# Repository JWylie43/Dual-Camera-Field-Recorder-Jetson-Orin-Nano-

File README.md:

# Orin Nano Stereo Recorder & Stitcher

An end-to-end field rig for a side-by-side stereo camera on a **Jetson Orin Nano**:
**record** a wide dual-camera feed, **calibrate** the two cameras, and **stitch** the
result into a single cylindrical panorama.

Built around the Arducam B0577 dual global-shutter kit (3840×1200 combined) in a
3D-printed housing, tuned to run for hours outdoors at **30 fps with the CPU
near-idle** (maximum thermal headroom).

---

## Project layout

```
orin-nano-recorder/
├── recorder/            Runs ON THE ORIN — capture + web control panel
│   ├── record.py          hardware-MJPEG → MKV recorder (GStreamer)
│   └── server.py          Flask web panel (Start/Stop, live preview, thermals, snapshots)
├── calibration/         Runs ON YOUR MAC/DESKTOP — ChArUco stereo calibration
│   ├── show_board.py      generate/display the ChArUco board
│   ├── calibrate.py       intrinsics (L+R) + stereo extrinsics from snapshots
│   ├── images/            calibration snapshots (git-ignored)
│   └── *_intrinsics.json, stereo_extrinsics.json   calibration results
├── stitching/           Runs ON YOUR MAC/DESKTOP — panorama stitcher (C++)
│   ├── stitch_pipeline.cpp   calibration-driven cylindrical stitch (image or video)
│   ├── CMakeLists.txt
│   └── include/json.hpp
├── 3d-housing-model/    Printable enclosure (Housing.zip)
└── setup.sh             Orin dependency install / L4T element check
```

## The workflow

1. **Record** on the Orin (`recorder/`) → combined `3840×1200` MKV on the NVMe, and
   full-res calibration snapshots via the web panel's Snapshot button.
2. **Calibrate** on your computer (`calibration/`) → per-camera intrinsics +
   the stereo extrinsic rotation between the two cameras (JSON files).
3. **Stitch** on your computer (`stitching/`) → feed a frame or video + the
   calibration and get a cylindrical panorama. Alignment is driven purely by the
   calibration — no feature matching.

---

# 1. Recorder (on the Orin)

`recorder/record.py` (CLI) and `recorder/server.py` (web panel).

## The one thing to understand first

**The Jetson Orin Nano (and Orin NX) have no hardware video encoder (no NVENC).**
That single fact drives every design decision here:

1. **No `nvv4l2h264enc` / `nvv4l2h265enc`** — they don't exist on this board. H.264/
   H.265 must be done in *software* (x264, CPU-heavy) or you use the **hardware JPEG
   engine (NVJPG)** for MJPEG. This project uses **MJPEG** so the CPU stays idle and
   the board runs cool — the right trade for a hot enclosure. (Files are bigger:
   ~40 GB/hr vs ~7 for H.264. A 500 GB drive holds ~12 hours.)

2. **Capture with `nvv4l2camerasrc`, never `v4l2src`.** Plain `v4l2src` copies every
   9 MB frame on one CPU thread, pegging a core and capping the pipeline at ~28 fps.
   `nvv4l2camerasrc` captures zero-copy into NVMM (GPU memory) → clean, sustained
   30 fps with the CPU barely moving. **This was the single fix that unblocked everything.**

3. **Every queue is `leaky=downstream`.** `nvvidconv` (the VIC) owns a tiny output
   buffer pool; a non-leaky queue behind it grabs all the buffers and *deadlocks* the
   pipeline. Leaky queues drop a frame under pressure instead of stalling.

4. **Stop with SIGINT, never SIGTERM/SIGKILL.** The MKV gets its duration + seek
   index only on a clean end-of-stream (`gst-launch -e` on SIGINT). Kill it any other
   way and you get an unfinalized file (`Duration: N/A`, won't scrub).

## Usage

```bash
cd recorder
# CLI recorder
python3 record.py                 # record until Enter / Ctrl+C
python3 record.py --seconds 30    # fixed duration
python3 record.py --measure --seconds 20         # benchmark fps, no disk write
python3 record.py --seconds 600 --log-thermals   # soak test + tegrastats log
python3 record.py --dry-run       # print the pipeline, don't run

# Web control panel
sudo python3 server.py            # sudo enables the "log thermals to file" toggle
```

Browse from a phone/laptop on the same network to **`http://<orin-ip>:8080`** (find
the IP with `hostname -I`, or use `http://<hostname>.local:8080`). The panel gives you
live preview (idle *and* recording), Start/Stop, elapsed time, live thermals, and a
**Snapshot** button that writes full-res stills to `/mnt/video/calib` for calibration.

## How it works

```
record.py builds & runs a GStreamer pipeline:
  nvv4l2camerasrc → NVMM,UYVY → nvvidconv → I420 → queue(leaky)
    → nvjpegenc → jpegparse → matroskamux → filesink            (the MKV)
  with --preview-port it tees a second branch to a tcpserversink (MJPEG preview)

server.py owns an idle-preview pipeline when stopped, hands the camera to record.py
  on Start, and relays the MJPEG to the browser at /preview.mjpg. Stop = SIGINT =
  clean finalize. The camera is single-open, so one pipeline holds it at a time.
```

## Auto-start on boot (systemd)

Run the panel as a service so it survives reboots. Point it at `recorder/server.py`
and use **`KillSignal=SIGINT`** so `systemctl stop` finalizes the current recording:

```ini
# /etc/systemd/system/camera-rig.service
[Unit]
After=network-online.target
Wants=network-online.target
[Service]
WorkingDirectory=/home/<user>/orin-nano-recorder/recorder
ExecStart=/usr/bin/python3 /home/<user>/orin-nano-recorder/recorder/server.py
Restart=on-failure
User=root
[Install]
WantedBy=multi-user.target
```
```bash
sudo systemctl daemon-reload && sudo systemctl enable --now camera-rig
```

For a **portable** rig, the Orin can broadcast its own Wi-Fi hotspot (NetworkManager
`ipv4.method shared`), so a phone/laptop connects directly at a fixed address with no
router. Give the Orin higher auto-connect priority on your home Wi-Fi so it rejoins
that when in range and falls back to the hotspot in the field.

---

# 2. Calibration (on your computer)

ChArUco-based stereo calibration. **Run on your Mac/desktop, not the Orin** — it needs
`opencv-contrib-python` (the `aruco` module):

```bash
pip install -U opencv-contrib-python numpy
```

## Steps

1. **Board.** `python3 calibration/show_board.py` generates/opens `charuco_board.png`
   (7×10, `DICT_5X5_1000`). **Print it** (matte, glued flat) — printing beats a screen
   (screens add glare/moiré that break detection). **Measure one black square with
   calipers** — you'll pass that size.
2. **Capture.** From the web panel, tap **Snapshot** ~30–40× with the board at varied
   angles/distances. Cover each camera's whole frame **and** get a good batch with the
   board centred where **both** cameras see it (that overlap set drives the extrinsics).
3. **Pull the shots** to `calibration/images/`:
   ```bash
   scp -r <user>@<orin-host>:/mnt/video/calib ./calibration/images
   ```
4. **Calibrate** (from `calibration/`, pass your measured board sizes in mm):
   ```bash
   python3 calibrate.py --square-mm 66.5 --marker-mm 48.5
   ```

Outputs `left_intrinsics.json`, `right_intrinsics.json`, `stereo_extrinsics.json`
(baseline in mm + rotation), plus undistort/rectified sample images.

- Intrinsics are **mount-independent**; extrinsics describe the **fixed housing** —
  re-run if the cameras are disturbed.
- To re-solve only the extrinsics from a fresh overlap batch without recomputing
  intrinsics: `python3 calibrate.py --use-intrinsics . --square-mm 66.5 --marker-mm 48.5`.
- Good result: RMS < ~1 px per camera and for the stereo solve, ≥80% frame coverage,
  ≥10 stereo views, and a baseline matching your real lens spacing.

---

# 3. Stitching (on your computer)

`stitching/stitch_pipeline.cpp` — a calibration-driven **cylindrical** stitcher. Reads
the calibration JSON and stitches the combined LEFT|RIGHT feed into one panorama.
**No feature detection** (no BRISK / findHomography); alignment is the extrinsic
rotation `R`. Per-frame work runs on `cv::UMat`, so it uses the **GPU via OpenCL**
when available and falls back to CPU otherwise — same source on macOS and desktop,
OpenCV 4.x or 5.x.

## Prerequisites

The stitcher is C++ and is built from source on your machine. You don't need to
build OpenCV yourself — a prebuilt package is fine. You need four things: a C++
compiler, CMake, OpenCV (4.x or 5.x), and FFmpeg (for `ffprobe`, used to count
video frames). Install per platform:

**macOS** (via [Homebrew](https://brew.sh)):
```bash
xcode-select --install          # C++ compiler (clang) — skip if already installed
brew install cmake opencv ffmpeg
```

**Windows** (x64):
1. **Visual Studio 2022** — install the *"Desktop development with C++"* workload
   (this is the compiler). The free Community edition is fine.
2. **CMake** — https://cmake.org/download (or `winget install Kitware.CMake`).
3. **OpenCV** — download the Windows build from https://opencv.org/releases,
   run the self-extractor, and extract to `C:\` so you get `C:\opencv`. Then set
   the env var CMake looks for, and add the DLL folder to PATH (PowerShell, Admin):
   ```powershell
   [Environment]::SetEnvironmentVariable("OpenCV_DIR", "C:\opencv\build", "Machine")
   [Environment]::SetEnvironmentVariable("Path", $env:Path + ";C:\opencv\build\x64\vc16\bin", "Machine")
   ```
   (If there's no `vc16` folder, use whatever `vcXX` exists under `C:\opencv\build\x64\`.)
4. **FFmpeg** — https://ffmpeg.org/download.html (or `winget install Gyan.FFmpeg`);
   make sure `ffprobe` is on your PATH.

**Linux** (Debian/Ubuntu):
```bash
sudo apt-get install -y build-essential cmake libopencv-dev ffmpeg
```

To confirm everything is present: `cmake --version`, `ffprobe -version`, and (macOS/Linux)
`pkg-config --modversion opencv4` or check that `C:\opencv\build\OpenCVConfig.cmake` exists.

## Build

```bash
cd stitching
cmake -S . -B build
cmake --build build --config Release      # --config Release matters on Windows
```

The binary lands at `build/StitchPipeline` (macOS/Linux) or
`build\Release\StitchPipeline.exe` (Windows). On Windows the project's
`CMakeLists.txt` already points at `C:/opencv/build`; override with
`-D OpenCV_DIR="<path>"` if yours lives elsewhere.

## Run

### One-click flow (recommended)

Run the binary with **no `--source`** and the browser tuner opens immediately:

```bash
./build/StitchPipeline          # opens the tuner; import + save happen in the page
```

In the page:
1. Click **Import source…** — a native file dialog opens; pick a video or image
   (anywhere on disk). The preview loads and the frame slider wires up.
2. Align the **far (top)** and **near (bottom)** edges.
3. *(Optional)* tick **crop to box** and drag the yellow box (move by its body,
   resize from the top-left / bottom-right handles) to keep only the region you
   want — trims the black undistortion borders and unneeded scenery. The render
   only processes that region, so it's faster and the output is smaller.
4. Click **Stitch all frames** — a native **Save as** dialog pops up to choose the
   output path + filename, then it renders the whole video there.

The dialogs are the OS's own: macOS uses `osascript` (Finder), Windows a
PowerShell `OpenFileDialog`/`SaveFileDialog`, Linux `zenity`. No wrapper script or
extra dependency — it's all in the one executable per platform.

**Double-click launchers** (build-on-first-run, then launch):
- **macOS:** `stitching/stitch.command` (Finder)
- **Windows:** `stitching/stitch.bat`

The program finds the `calibration/` folder **relative to its own executable**
(searching upward), so it works no matter what directory it's launched from —
double-clicking the built `StitchPipeline` / `StitchPipeline.exe` directly works
too. Use `--calib-dir <path>` to point elsewhere.

### Direct CLI

```bash
# single image → pipeline_out/pano.jpg (+ overlap_5050.jpg)
./build/StitchPipeline --source ../calibration/images/calib_114.jpg

# video → pipeline_out/stitched_video.mp4
./build/StitchPipeline --source recording.mp4 --start 300 --end 900
```

Source type is auto-detected: images stitch one frame; videos (`.mp4/.mkv/.mov/...`)
loop frames. The remap maps depend only on the calibration, so they're built once and
reused for every frame.

| Flag | Default | Meaning |
|---|---|---|
| `--source PATH` | (required) | Combined LEFT\|RIGHT image or video (alias `--image`) |
| `--calib-dir DIR` | `../calibration` | Folder with the intrinsics/extrinsics JSON |
| `--out DIR` | `pipeline_out` | Output folder (file named `stitched_video.mp4` / `pano.jpg`) |
| `--out-file PATH` | — | Full output path incl. filename; overrides `--out`. Parent dirs are created. Used by the launcher's output picker |
| `--crop x,y,w,h` | — | Restrict stitching to this rectangle (in panorama pixels) — trims black borders/scenery and speeds up rendering (warp + blend + encode only process the crop). The tuner's "crop to box" sets this visually. Seam + exposure still use the full overlap, which is always inside the crop |
| `--start N` / `--end N` | `0` / `-1` | Video frame range (`-1` = end) |
| `--degrees D` | `0` | Horizon roll correction |
| `--seam X` | auto | Straight-seam column (default: overlap centre). Only used when smart seam is off (`--no-smart-seam` + `--bands 0`) |
| `--shift-top N` | `0` | Horizontal shift of the right image's **top** rows (aligns the **far** edge) |
| `--shift-bottom N` | `0` | Horizontal shift of the **bottom** rows (aligns the **near** edge) |
| `--shift-y N` | `0` | Vertical shift of the right image |
| `--shift-x N` | `0` | Convenience: sets both top and bottom to N (plain horizontal shift) |
| `--bands N` | `6` | Multi-band (Laplacian) blend levels — smooths the seam *without* blurring detail; `0` = hard seam |
| `--no-exposure` | (exposure match **on** by default) | Matches the right image's brightness/color to the left (per-channel gain measured in the overlap) — for when one camera faces brighter light. Pass `--no-exposure` to turn it off |
| `--no-smart-seam` | (smart seam **on** by default) | Smart seam routes through the min-difference path so it weaves *around* moving objects — reduces player ghosting/duplication at the seam. Auto-searches the known overlap region (no `--seam` needed), biased toward the overlap centre, and is temporally stabilised so it stays put frame-to-frame (won't jitter with tripod sway) unless a moving object makes a detour clearly cheaper. Pass `--no-smart-seam` to turn it off |
| `--tune` | off | Launch the interactive browser tuner (see below) |
| `--port N` | `8090` | Port for the `--tune` web server |

If `--shift-top` ≠ `--shift-bottom`, the right image is **sheared** — the per-row
horizontal shift is interpolated between them. This aligns a **receding field**
(near edge at the bottom, far edge at the top) along a straight vertical seam:
dial `--shift-bottom` for the front of the field and `--shift-top` for the back.

### Interactive tuning (`--tune`)

Rotation-only alignment is exact only at infinity; at finite distance a small
horizontal **shift** can sharpen a chosen plane (e.g. a screen). `--tune` gives you
a one-command visual tuner:

```bash
./build/StitchPipeline --source <image-or-video> --tune
```

This warps the first frame, starts a tiny localhost web server, and **opens your
browser** to a live tuner. There you:
- adjust **Shift far (top)**, **Shift near (bottom)**, **Shift-y**, and **Seam** with
  the **◀ ▶** arrows or by typing (←/→ shifts both top & bottom together; `[` `]`
  moves the seam) over a live stitched preview — align the far and near edges of the
  field so the whole thing lines up under a straight vertical seam. Leave
  **multi-band blend** on to smooth the join in the output (it keeps detail sharp,
  unlike a linear feather), and enable **exposure/color match** if one camera faces
  brighter light, and turn on **seam avoidance** if players ghost/duplicate at the
  seam (it routes the cut around moving objects); the preview shows the raw seam so
  you can align precisely, and blend/exposure/seam-avoidance apply to the output,
- **for a video**, use the **Frame** slider, its ◀ ▶, or the frame box to jump to
  any frame and align on it — the current frame and total (`N / 1591`) are shown.
  The total comes from `ffprobe` packet-counting (fast, exact for MJPEG even when the
  container reports no frame count); if `ffprobe` isn't available, the frame box +
  prev/next still work, just without a fixed slider range. (These recordings can't be
  seeked, so frames are reached by reading sequentially — scrubbing **forward** is
  fast; a big jump **backward** re-reads from the start and takes a moment.)
- every value is a **typeable box** — click the ◀ ▶ arrows or just type a number,
- toggle **overlap blend** (50/50) to check alignment,
- click **Stitch all frames** to run the full stitch on the whole image/video with
  the current values — a **progress bar** tracks it and a **✅ Done** message shows
  the saved path when finished (no need to re-run anything),
- click **Finish & stop** (appears when done) or **Quit** to stop the server so the
  terminal command exits; then close the tab.

For a video it previews/​tunes on the first frame (or `--start N`), then applies your
chosen shift/seam to every frame. You can also skip the UI and pass the values
directly: `--shift-x N --seam X`. Use `--port N` if 8090 is taken.

> **Exposure/seam:** in high-contrast scenes the seam can show a brightness step (one
> camera facing a bright window). Exposure compensation + seam feathering are future
> additions; on evenly-lit footage it isn't an issue.

---

## Hardware / prerequisites (Orin)

- Jetson Orin Nano (or NX) with JetPack / L4T.
- Arducam B0577 stereo kit (or any V4L2 camera that outputs **UYVY** over CSI). Install
  the vendor driver first — confirm with `v4l2-ctl --list-formats-ext` (expect
  `UYVY 3840x1200`).
- An NVMe mounted at **`/mnt/video`**, writable by your user.
- NVIDIA L4T GStreamer elements (`nvv4l2camerasrc`, `nvvidconv`, `nvjpegenc`) — ship
  with JetPack.

Install on the Orin:
```bash
git clone <your-repo-url> orin-nano-recorder
cd orin-nano-recorder
./setup.sh          # apt deps + checks the L4T elements are present
```

> **Different camera/resolution?** Edit the `Config` in `recorder/record.py` (and the
> preview caps in `recorder/server.py`). Camera-agnostic as long as the source is a
> V4L2 YUV device.

### Tested environment

| Component | Tested version |
|---|---|
| Board | Jetson Orin Nano Developer Kit |
| JetPack | 6.2 (L4T R36.4.3, kernel 5.15.148-tegra) |
| OS | Ubuntu 22.04 (jammy), arm64 |
| Python / GStreamer / Flask | 3.10 / 1.20.3 / 2.0.1 |
| Camera | Arducam B0577 dual global-shutter (2.3 MP × 2, onboard ISP) |
| Stitcher OpenCV | 4.x or 5.x (built per machine) |

**Kernel pinning (important):** the Arducam driver is a kernel package built for the
exact kernel/L4T. Don't `apt upgrade` the kernel without a matching Arducam build, or
the camera stops enumerating after reboot. Pin the kernel, or upgrade both together.

---

## Playback

MJPEG-in-MKV doesn't open in some default players. **Use VLC:**
```bash
sudo apt install -y vlc
xdg-mime default vlc.desktop video/x-matroska
```

## Troubleshooting (recorder)

| Symptom | Cause / fix |
|---|---|
| Caps "not-negotiated" at start | Camera doesn't offer that format/res — check `v4l2-ctl --list-formats-ext`. |
| One core at 100%, ~26–28 fps | You're using `v4l2src`. Switch to `nvv4l2camerasrc`. |
| Pipeline freezes, one core spinning | Non-leaky `queue` after `nvvidconv` deadlocked the VIC pool. Use `leaky=downstream`. |
| `Duration: N/A`, won't scrub in VLC | File wasn't finalized — killed with SIGTERM. Stop with SIGINT (Enter/Ctrl-C). |
| Green / tiny file | No real camera signal — check the ribbon and driver. |
| `nvv4l2h265enc` missing | Expected on Orin Nano/NX (no NVENC). Use MJPEG. |

## Troubleshooting (calibration / stitching)

| Symptom | Cause / fix |
|---|---|
| `No module named cv2.aruco` | `pip install -U opencv-contrib-python` (calibration needs contrib). |
| 0 stereo views / no overlap | Board never fully visible to both cameras at once — get it centred and big in **both** preview halves; print it (screens fail). |
| Baseline scale looks wrong | `--square-mm`/`--marker-mm` must match the **measured** printed board. |
| Stitch seam ghosting on near objects | Parallax from the baseline — unavoidable rotation-only; minimal on distant scenes. |
| CMake: "Could NOT find OpenCV" | OpenCV isn't installed or not found. Install it (see Prerequisites), or pass `-D OpenCV_DIR="<dir containing OpenCVConfig.cmake>"`. |
| Windows: app exits with "opencv_world….dll not found" | The OpenCV `bin` folder isn't on PATH. Add `C:\opencv\build\x64\vc16\bin` to PATH (see Prerequisites) or copy the DLL next to the exe. |
| Frame slider shows `/ ?` (unknown total) | `ffprobe` isn't on PATH — install FFmpeg. Stitching still works; only the frame count is unknown. |

---

## License

MIT — see `LICENSE`.

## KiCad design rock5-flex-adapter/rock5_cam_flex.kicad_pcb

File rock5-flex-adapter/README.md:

# RPi HQ Camera → Radxa Rock 5B+ CAM0 — Flex PCB Adapter

Single-piece flexible PCB that connects a Raspberry Pi HQ Camera (IMX477,
15-pin 1.0 mm FFC) to a Radxa Rock 5B+ CAM0 port (31-pin 0.3 mm FFC).
Bare gold fingers at both ends (no connectors mounted); a stiffened
component island mid-ribbon carries a TXS0104E I²C/EN level translator
(Rock side is 1.8 V, camera side is 3.3 V) and an XC6206 1.8 V LDO.

**Status: FIRST PASS, generated.** ERC 0/0, DRC 0/0 (all severities),
netlist verified pin-for-pin against the spec table — but several physical
parameters are placeholders. Do NOT order boards before the human
checklist below is complete.

## Files

| File | What |
|---|---|
| `rock5_cam_flex.kicad_pro/.kicad_sch/.kicad_pcb` | KiCad project (authored in KiCad-8-compatible format, saved/validated with KiCad 10.0.6) |
| `flexadapter.kicad_sym`, `footprints.pretty/` | project-local libraries (see `sym-lib-table` / `fp-lib-table`) |
| `rock5_cam_flex.net` | exported netlist (kicadsexpr) |
| `bom.csv` | BOM with LCSC numbers for U1/U2 |
| `fabrication-notes.txt` | flex stackup, stiffeners, bend zones, verification list |
| `tools/generate_fingers.py` | parametric finger footprint generator (keep — pad dims are placeholders) |
| `tools/generate_schematic.py` | schematic generator (plain python3) |
| `tools/generate_pcb.py` | PCB generator (run with KiCad's bundled python, see file header) |
| `tools/adapter_netlist.py` | single source of truth for connectivity |
| `tools/check_netlist.py` | asserts the exported netlist against the spec table |

Regenerate everything:

```bash
cd tools
python3 generate_fingers.py
python3 generate_schematic.py
/Applications/KiCad/KiCad.app/Contents/Frameworks/Python.framework/Versions/Current/bin/python3 generate_pcb.py
cd ..
kicad-cli sch erc rock5_cam_flex.kicad_sch --severity-all --output erc.rpt
kicad-cli sch export netlist --format kicadsexpr --output rock5_cam_flex.net rock5_cam_flex.kicad_sch
python3 tools/check_netlist.py
kicad-cli pcb drc rock5_cam_flex.kicad_pcb --severity-all --output drc.rpt
```

## What is verified

- **Netlist** — every row of the spec table asserted by `tools/check_netlist.py`
  (MIPI pairs direct, I²C/EN through the correct TXS0104E channels with 0R
  insurance resistors, VCCA=1.8 V ≤ VCCB=3.3 V, J1 pins 30/31 (5V) and all
  other NC pins verified unconnected).
- **TXS0104E / XC6206 pinouts** — checked against the TI datasheet
  (SCES651K, D/PW package table) and Torex XC6206 SOT-23 pinout.
- **ERC and DRC** — 0 errors, 0 warnings, 0 unconnected items (with the
  relaxed flex design rules described in the fab notes).
- **MIPI intra-pair skew** — computed from actual track geometry and
  trombone-matched: D0 = 0 µm, D1 = 41 µm, CLK = 41 µm (target ±100 µm).
  Inter-pair spread ≈ 2.4 mm (spec allows ±2 mm loosely — acceptable).

## What is PLACEHOLDER / unverified (human checklist before ordering)

1. **Finger pad dimensions** (width/length/tab width at both ends) — verify
   against SHETIME FPC31-T1S1-2023-AC (LCSC C53403949), Molex 15031-0431,
   and a caliper-measured genuine RPi camera ribbon; then edit
   `tools/generate_fingers.py` and regenerate.
2. **Contact-face orientation** — both finger fields are copper-up (same
   side as components), and the 15P footprint bakes in a pin-1 mirroring
   choice. Confirm against both receptacles' contact sides and the ribbon
   bend path; mirror an end if required (`pin1` parameter in the generator).
3. **Ribbon length** — currently 80 mm (`RIBBON_LEN` in `generate_pcb.py`,
   spec range 60–100 mm). Set the final length before fab; the lane
   routing scales automatically, re-run and re-check DRC.
4. **Impedance** — not controlled; see fab notes.
5. **Fab capability** — 0.08 mm min clearance, 0.10 mm min track,
   0.35/0.15 vias. Standard for flex vendors but confirm.

## Deviations from the spec (all deliberate, review each)

- **"No vias on MIPI" is physically impossible here**: Rock CAM0 orders the
  pairs (top→bottom) D1, D0, CLK; the camera wants D0, D1, CLK. One pair
  must cross the other, and a 2-layer board can only do that with a layer
  swap. The **D0 pair does one short B.Cu hop at the J1 escape** (4 vias,
  0.35/0.15, x = 3.6–7.7 mm, outside the bend zones); D1 and CLK never
  leave F.Cu. The hatch is continuous under the hop. If the human mirrors
  an end during orientation verification, re-check whether the crossing
  disappears (some orientation combinations don't need it).
- **GND fingers 13/16/19 (J1) have no stitching vias** — at 0.3 mm pitch,
  between live MIPI rows, no 0.35 mm via fits. They run the full ribbon as
  F.Cu **shield traces between the MIPI pairs** (a signal-integrity bonus)
  and join the GND fingers at the roomy 1.0 mm end. GND 1/4/7/10/21 have
  normal escape+via stitching; one 0.10 mm-wide squeeze on the GND13 trace
  passes the D0 escape.
- **C5/C6 ("camera-end" decoupling) sit at the island exit** (~25 mm from
  J2) rather than adjacent to J2: the spec also demands "no component pads
  on unreinforced flex", and the J2 tab stiffener is the insertion tip.
  The camera module has its own local decoupling; C5/C6 serve as bulk for
  the cable run. If true J2-adjacent decoupling is wanted, add a fourth
  stiffener zone in the taper and move them.
- **TP3 added** (not in the spec BOM): the spec's JP1 connects J1.27
  (CM_RST_L_1) "to a test pad" — TP3 is that pad.
- **R1 pulls OE up to VCCA** — per the spec's own deviation note: no
  controller exists on this cable to drive OE; always-enabled is intended
  (noted on the schematic sheet).

## Design overview

```
x=0                 9      19  22            56  57     67  68  71      80
|31P fingers|--gap--|BEND A|---|== ISLAND ==|---|BEND B|---|taper|15P fingers|
 (Rock CAM0)                    U1 TXS0104E                       (RPi camera)
                                U2 XC6206 1.8V
```

- MIPI on the −y half: D0 (top lanes), D1 (inner lanes), CLK (stays on its
  J1 pad rows), each pair 0.15/0.15 coupled, GND shield traces between them.
- I²C/EN/power on the +y half through the island: J1 (1.8 V) → U1 A-side;
  U1 B-side (3.3 V) → R2/R3/R4 (0R) → J2. XVS spare channel broken out to
  TP1 (1.8 V) / TP2 (3.3 V). 3V3 trunk 0.4 mm.
- B.Cu: cross-hatched GND (0.2/0.3 mm, 45°), brief B.Cu hops only for
  CAM_EN (×2), VCCB feed, VCC_1V8 distribution and the D0 swap.

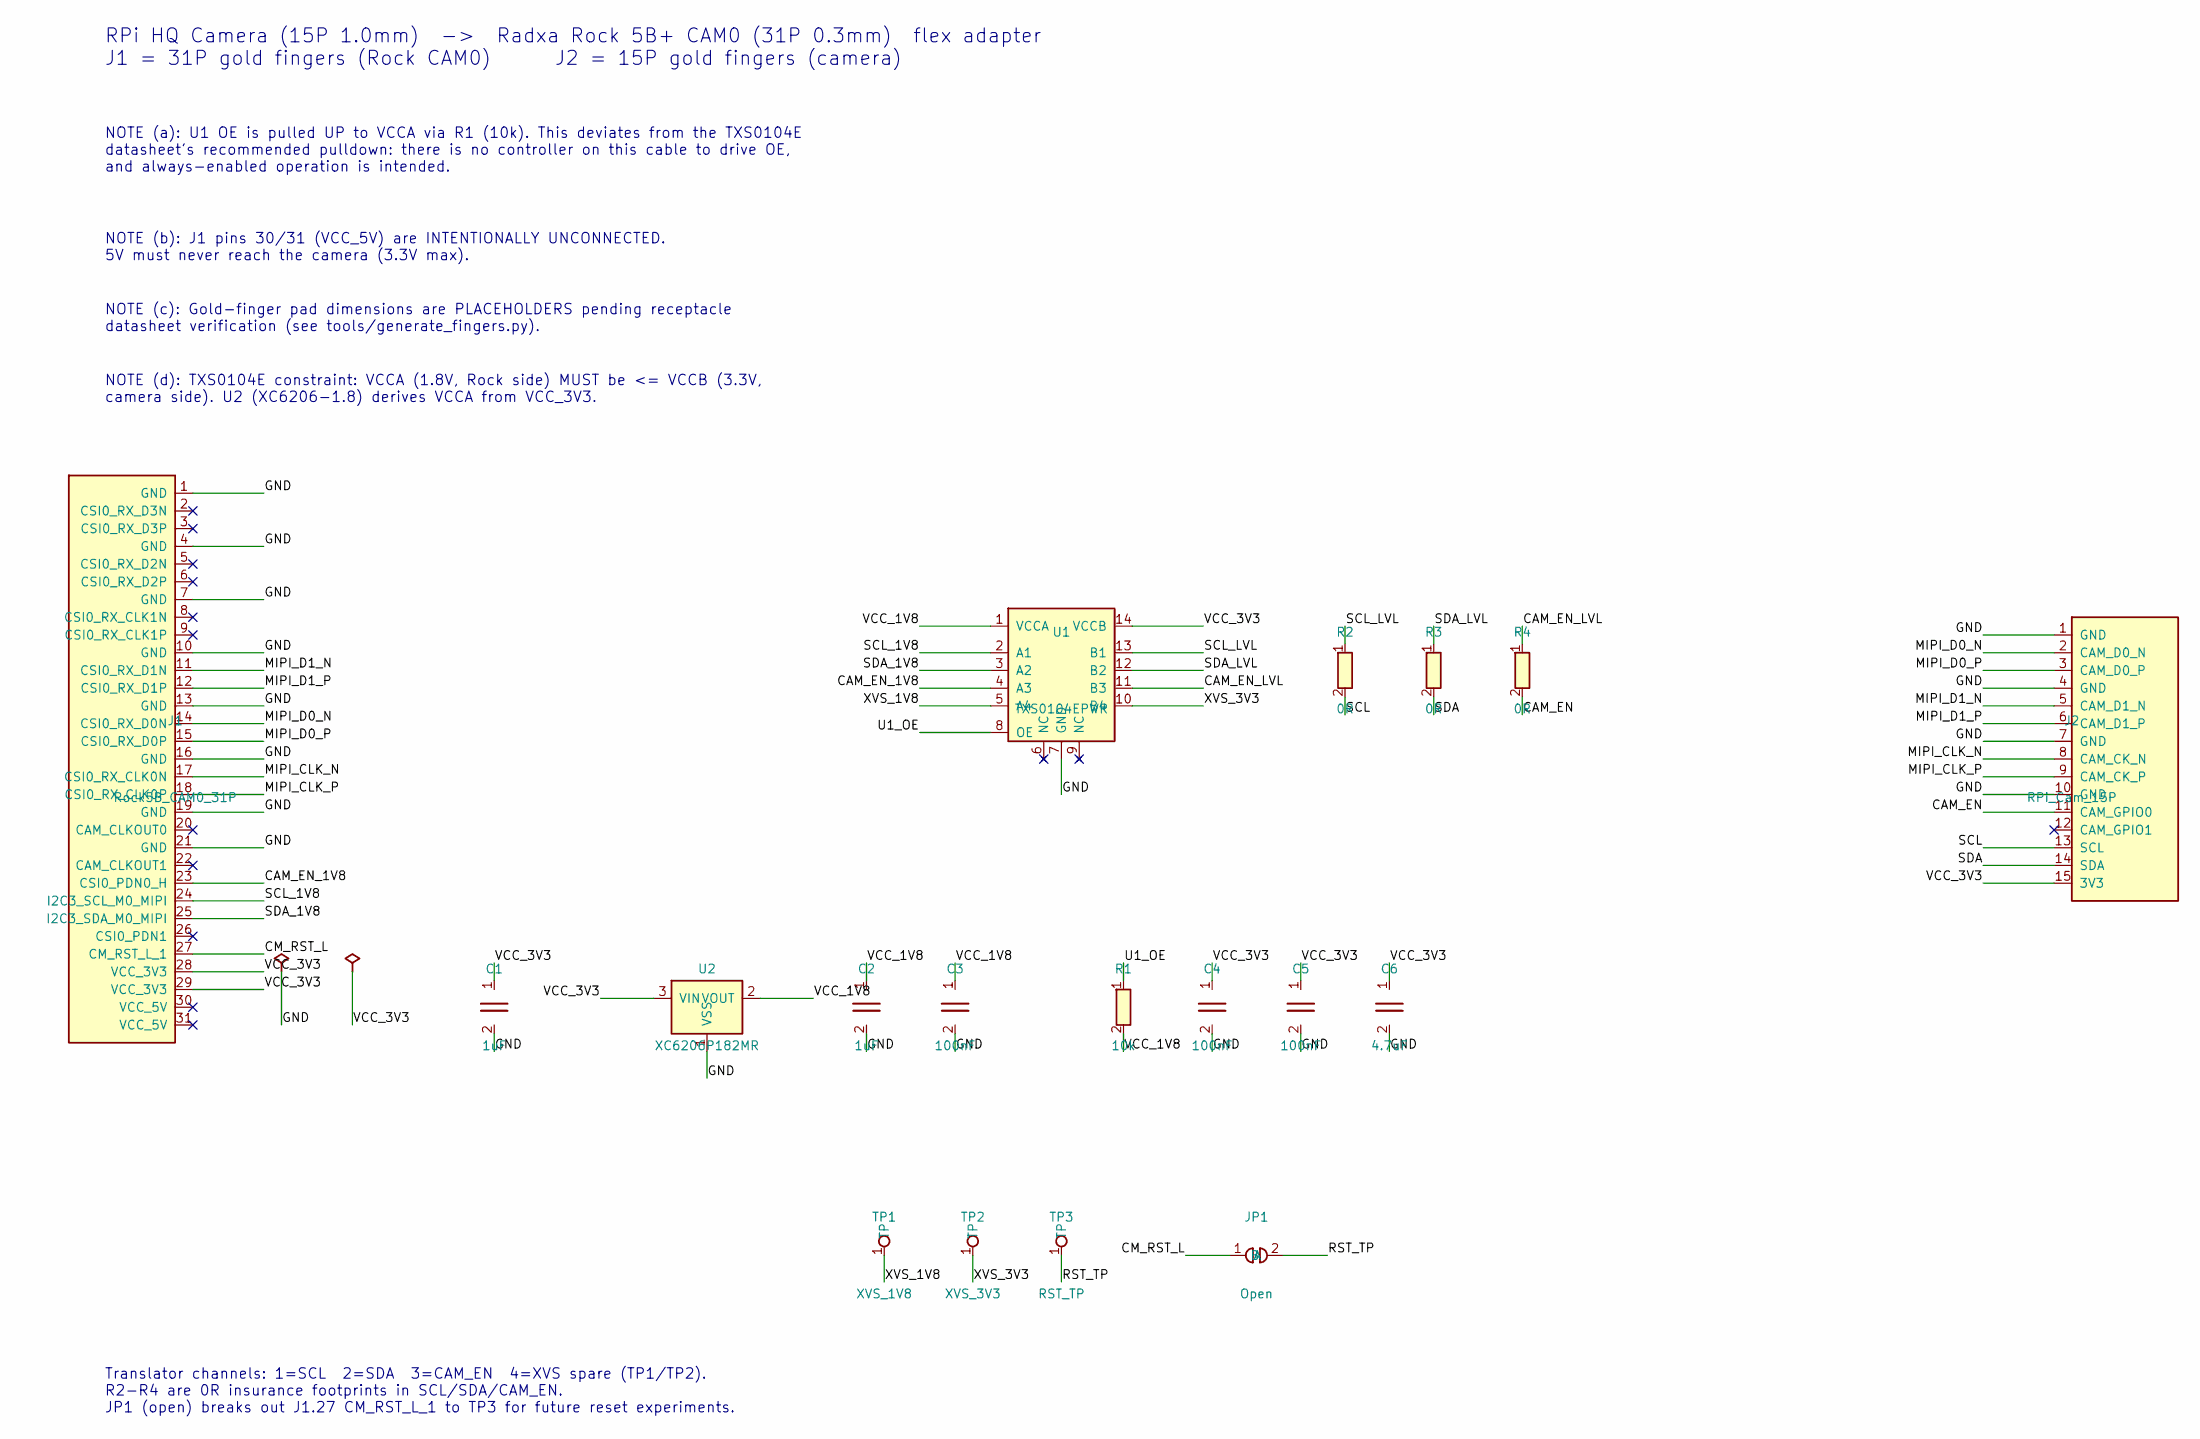
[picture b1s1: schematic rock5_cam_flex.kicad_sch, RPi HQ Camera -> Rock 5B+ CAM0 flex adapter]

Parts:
C1, C2: 1uF; C_0402_1005Metric
C3, C4, C5: 100nF; C_0402_1005Metric
C6: 4.7uF; C_0603_1608Metric
J1: Rock5B_CAM0_31P; Flex_Finger_31P_0.3mm
J2: RPi_Cam_15P; Flex_Finger_15P_1.0mm
JP1: Open; SolderJumper-2_P1.3mm_Open_RoundedPad1.0x1.5mm
R1: 10k; R_0402_1005Metric
R2, R3, R4: 0R; R_0402_1005Metric
TP1: XVS_1V8; TestPoint_Pad_1.5x1.5mm
TP2: XVS_3V3; TestPoint_Pad_1.5x1.5mm
TP3: RST_TP; TestPoint_Pad_1.5x1.5mm
U1: TXS0104EPWR; TSSOP-14_4.4x5mm_P0.65mm; LCSC C44955
U2: XC6206P182MR; SOT-23-3; LCSC C347373

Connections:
CAM_EN: J2.11 (CAM_GPIO0), R4.2
CAM_EN_1V8: J1.23 (CSI0_PDN0_H), U1.4 (A3)
CAM_EN_LVL: R4.1, U1.11 (B3)
CM_RST_L: J1.27 (CM_RST_L_1), JP1.1 (A)
GND: C1.2, C2.2, C3.2, C4.2, C5.2, C6.2, J1.1 (GND), J1.4 (GND), J1.7 (GND), J1.10 (GND), J1.13 (GND), J1.16 (GND), J1.19 (GND), J1.21 (GND), J2.1 (GND), J2.4 (GND), J2.7 (GND), J2.10 (GND), U1.7 (GND), U2.1 (VSS)
MIPI_CLK_N: J1.17 (CSI0_RX_CLK0N), J2.8 (CAM_CK_N)
MIPI_CLK_P: J1.18 (CSI0_RX_CLK0P), J2.9 (CAM_CK_P)
MIPI_D0_N: J1.14 (CSI0_RX_D0N), J2.2 (CAM_D0_N)
MIPI_D0_P: J1.15 (CSI0_RX_D0P), J2.3 (CAM_D0_P)
MIPI_D1_N: J1.11 (CSI0_RX_D1N), J2.5 (CAM_D1_N)
MIPI_D1_P: J1.12 (CSI0_RX_D1P), J2.6 (CAM_D1_P)
RST_TP: JP1.2 (B), TP3.1
SCL: J2.13 (SCL), R2.2
SCL_1V8: J1.24 (I2C3_SCL_M0_MIPI), U1.2 (A1)
SCL_LVL: R2.1, U1.13 (B1)
SDA: J2.14 (SDA), R3.2
SDA_1V8: J1.25 (I2C3_SDA_M0_MIPI), U1.3 (A2)
SDA_LVL: R3.1, U1.12 (B2)
U1_OE: R1.1, U1.8 (OE)
VCC_1V8: C2.1, C3.1, R1.2, U1.1 (VCCA), U2.2 (VOUT)
VCC_3V3: C1.1, C4.1, C5.1, C6.1, J1.28 (VCC_3V3), J1.29 (VCC_3V3), J2.15 (3V3), U1.14 (VCCB), U2.3 (VIN)
XVS_1V8: TP1.1, U1.5 (A4)
XVS_3V3: TP2.1, U1.10 (B4)

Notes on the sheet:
RPi HQ Camera (15P 1.0mm) -> Radxa Rock 5B+ CAM0 (31P 0.3mm) flex adapter J1 = 31P gold fingers (Rock CAM0) J2 = 15P gold fingers (camera)
NOTE (a): U1 OE is pulled UP to VCCA via R1 (10k). This deviates from the TXS0104E datasheet's recommended pulldown: there is no controller on this cable to drive OE, and always-enabled operation is intended.
NOTE (b): J1 pins 30/31 (VCC_5V) are INTENTIONALLY UNCONNECTED. 5V must never reach the camera (3.3V max).
NOTE (c): Gold-finger pad dimensions are PLACEHOLDERS pending receptacle datasheet verification (see tools/generate_fingers.py).
NOTE (d): TXS0104E constraint: VCCA (1.8V, Rock side) MUST be <= VCCB (3.3V, camera side). U2 (XC6206-1.8) derives VCCA from VCC_3V3.
Translator channels: 1=SCL 2=SDA 3=CAM_EN 4=XVS spare (TP1/TP2). R2-R4 are 0R insurance footprints in SCL/SDA/CAM_EN. JP1 (open) breaks out J1.27 CM_RST_L_1 to TP3 for future reset experiments.

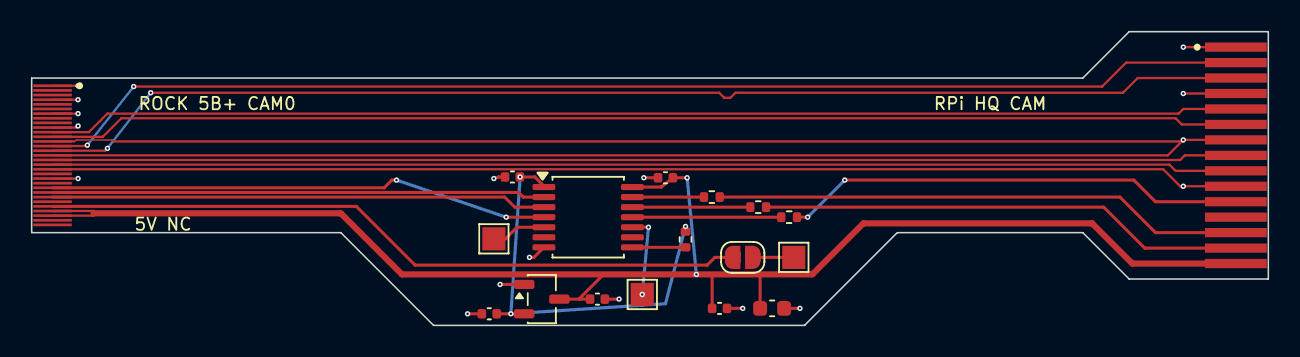
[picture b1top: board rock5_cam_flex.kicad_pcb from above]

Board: 2 copper layers, 80.0 x 19.0 mm, 18 parts (0 on the bottom side), 23 nets.

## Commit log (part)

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2026-06-30 Orin Nano stereo MJPEG recorder + web control panel
2026-06-30 README: tested environment & exact version requirements
